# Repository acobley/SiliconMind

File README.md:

View this project on [CADLAB.io](https://cadlab.io/node/794). 

# SiliconMind
PCB3 is a test release.  
**Do not use** . Unwired airwire on PCB.
Use the hardware files

Pure Keys aec-pcb3.sch
Pure Keys aec-pcb3.brd

PCB2 is a working release.  Use the hardware files

Pure Keys aec-pcb2.sch
Pure Keys aec-pcb2.brd

**make sure that the 20 way header(keyboard connector) is soldered on so the connector is on the otherside of the board to the components. **

**Button 1** controls the mode. Starts in Polyphonc mode.  
Press once (2 flashes) for split mode.  CV1/Trig1 is lower half of keyboard. CV2/Trig2 is upper
Press again (3 flashes for mono mode.  CV1/Trig 1 only
Press again (1 flash) to return to poly mode.

**Button 2* is record/play mode
Press and hold (button flashes when ready) to enter record mode.  The note on each trig in will be recorded (up to 64), the note length is **not** recorded.  When finished press once to exit record mode.   Press once (quickly) to enter play mode.

For step type recording use a manual trigger press.

**Note** Will only record the bottom note, best used in Mono mode for recording.   In playback mode will output on CV1/Trig1 and other notes are shifted up one.  In Split mode upper half of keyboard is available.

**Glide** 
Controls the Portamento rate.  Works in Mono/Poly mode.  In Split mode only upper half of keyboard is glided.

-------------------------------------------------------------------

This is a project to create a voltage control keyboard for Eurorack Synths.  The aim is to create a fourvoice polyphtonic keyboard, with no MIDI at all.

The hardware is based around the ATMEGA.

See alos Changelog.txt in Hardware

Software 

SiliconMind.ion is latest for aec-pcb2 First PCB hardware

                  Work in progress, in test !

Hardware Designs:

Pure Keys aec Original Design

Pure Keys aec-pcb1 First PCB  do not use

      	       Needs pull down resistors on	MK lines
                   5V Ref needs	 replacing with 3v version
                   Switch needs	 pull up, not down.
Pure Keys aec-pcb2. 

                   Changes in pcb1 are rolled into this
                   Pure Keys aec-pcb2 In Progress

Pure Keys aec-pcb3-inProgress (obsolete)

	Next design in progress
	     	    Changes from pcb2 are rolled into this 
		    
Pure Keys aec-pcb3-smd-inProgress 

	SMD version.   Next design in progress
	     	    Changes from pcb2 are rolled into this 
Pure Keys aec-pcb3 

	SMD version.   **Do not use** Unwired airwire on PCB.
	
	     	    Changes from pcb2 are rolled into this

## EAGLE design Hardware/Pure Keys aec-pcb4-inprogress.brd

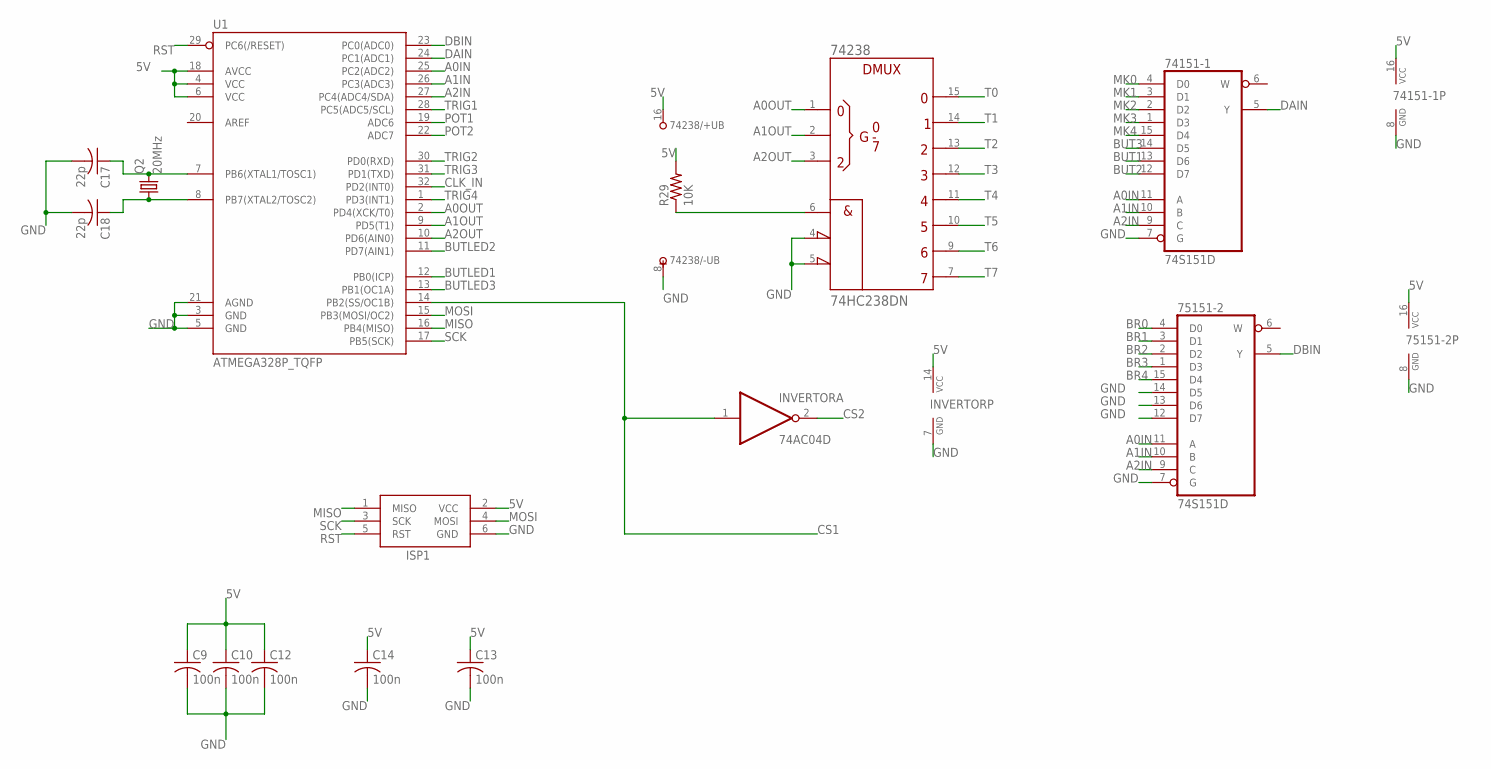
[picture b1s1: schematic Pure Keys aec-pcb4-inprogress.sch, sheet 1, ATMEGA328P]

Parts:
74151-1, 75151-2: 74S151D; SO16
74238: 74HC238DN; SO16
C9, C10, C12, C13, C14: 100n; C0805K
C17, C18: 22p; C0805K
INVERTOR: 74AC04D; SO14
ISP1: AVRISP-6; AVRISP
Q2: 20MHz; HC49UP
R29: 10K; R0805
U1: ATMEGA328P_TQFP; TQFP32-08

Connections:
5V: 74151-1.16 (VCC), 74238.16 (+UB), 75151-2.16 (VCC), C9.1, C10.1, C12.1, C13.1, C14.1, INVERTOR.14 (VCC), ISP1.2 (VCC), R29.2, U1.4 (VCC), U1.6 (VCC), U1.18 (AVCC); also elsewhere on the board
A0IN: 74151-1.11 (A), 75151-2.11 (A), U1.25 (PC2(ADC2))
A0OUT: 74238.1 (A), U1.2 (PD4(XCK/T0))
A1IN: 74151-1.10 (B), 75151-2.10 (B), U1.26 (PC3(ADC3))
A1OUT: 74238.2 (B), U1.9 (PD5(T1))
A2IN: 74151-1.9 (C), 75151-2.9 (C), U1.27 (PC4(ADC4/SDA))
A2OUT: 74238.3 (C), U1.10 (PD6(AIN0))
BR0: 75151-2.4 (D0); also elsewhere on the board
BR1: 75151-2.3 (D1); also elsewhere on the board
BR2: 75151-2.2 (D2); also elsewhere on the board
BR3: 75151-2.1 (D3); also elsewhere on the board
BR4: 75151-2.15 (D4); also elsewhere on the board
BUT1: 74151-1.13 (D6); also elsewhere on the board
BUT2: 74151-1.12 (D7); also elsewhere on the board
BUT3: 74151-1.14 (D5); also elsewhere on the board
BUTLED1: U1.12 (PB0(ICP)); also elsewhere on the board
BUTLED2: U1.11 (PD7(AIN1)); also elsewhere on the board
BUTLED3: U1.13 (PB1(OC1A)); also elsewhere on the board
CLK_IN: U1.32 (PD2(INT0)); also elsewhere on the board
CS1: INVERTOR.1 (I), U1.14 (PB2(SS/OC1B)); also elsewhere on the board
CS2: INVERTOR.2 (O); also elsewhere on the board
DAIN: 74151-1.5 (Y), U1.24 (PC1(ADC1))
DBIN: 75151-2.5 (Y), U1.23 (PC0(ADC0))
ENOUT1: 74238.6 (G1), R29.1
GND: 74151-1.7 (G), 74151-1.8 (GND), 74238.4 (!G2A), 74238.5 (!G2B), 74238.8 (-UB), 75151-2.7 (G), 75151-2.8 (GND), 75151-2.12 (D7), 75151-2.13 (D6), 75151-2.14 (D5), C9.2, C10.2, C12.2, C13.2, C14.2, C17.2, C18.2, INVERTOR.7 (GND), ISP1.6 (GND), U1.3 (GND), U1.5 (GND), U1.21 (AGND); also elsewhere on the board
MISO: ISP1.1 (MISO), U1.16 (PB4(MISO))
MK0: 74151-1.4 (D0); also elsewhere on the board
MK1: 74151-1.3 (D1); also elsewhere on the board
MK2: 74151-1.2 (D2); also elsewhere on the board
MK3: 74151-1.1 (D3); also elsewhere on the board
MK4: 74151-1.15 (D4); also elsewhere on the board
MOSI: ISP1.4 (MOSI), U1.15 (PB3(MOSI/OC2)); also elsewhere on the board
unnamed: C17.1, Q2.2, U1.7 (PB6(XTAL1/TOSC1))
unnamed: C18.1, Q2.1, U1.8 (PB7(XTAL2/TOSC2))
POT1: U1.19 (ADC6); also elsewhere on the board
POT2: U1.22 (ADC7); also elsewhere on the board
RST: ISP1.5 (RST), U1.29 (PC6(/RESET))
SCK: ISP1.3 (SCK), U1.17 (PB5(SCK)); also elsewhere on the board
T0: 74238.15 (Y0); also elsewhere on the board
T1: 74238.14 (Y1); also elsewhere on the board
T2: 74238.13 (Y2); also elsewhere on the board
T3: 74238.12 (Y3); also elsewhere on the board
T4: 74238.11 (Y4); also elsewhere on the board
T5: 74238.10 (Y5); also elsewhere on the board
T6: 74238.9 (Y6); also elsewhere on the board
T7: 74238.7 (Y7); also elsewhere on the board
TRIG1: U1.28 (PC5(ADC5/SCL)); also elsewhere on the board
TRIG2: U1.30 (PD0(RXD)); also elsewhere on the board
TRIG3: U1.31 (PD1(TXD)); also elsewhere on the board
TRIG4: U1.1 (PD3(INT1)); also elsewhere on the board

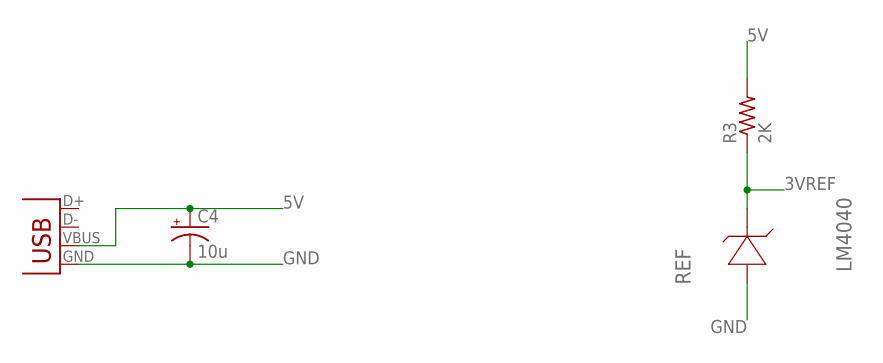
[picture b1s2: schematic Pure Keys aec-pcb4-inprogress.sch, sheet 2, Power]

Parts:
C4: 10u; 153CLV-0505
JP2: USB-B; USB-B-PTH
R3: 2K; R0805
REF: LM4040; SOT95P237X112-3N; MPN LM4040A30IDBZT

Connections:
3VREF: R3.1, REF.1 (CATHODE); also elsewhere on the board
5V: C4.+, JP2.VBUS, R3.2; also elsewhere on the board
GND: C4.-, JP2.GND, REF.2 (ANODE); also elsewhere on the board

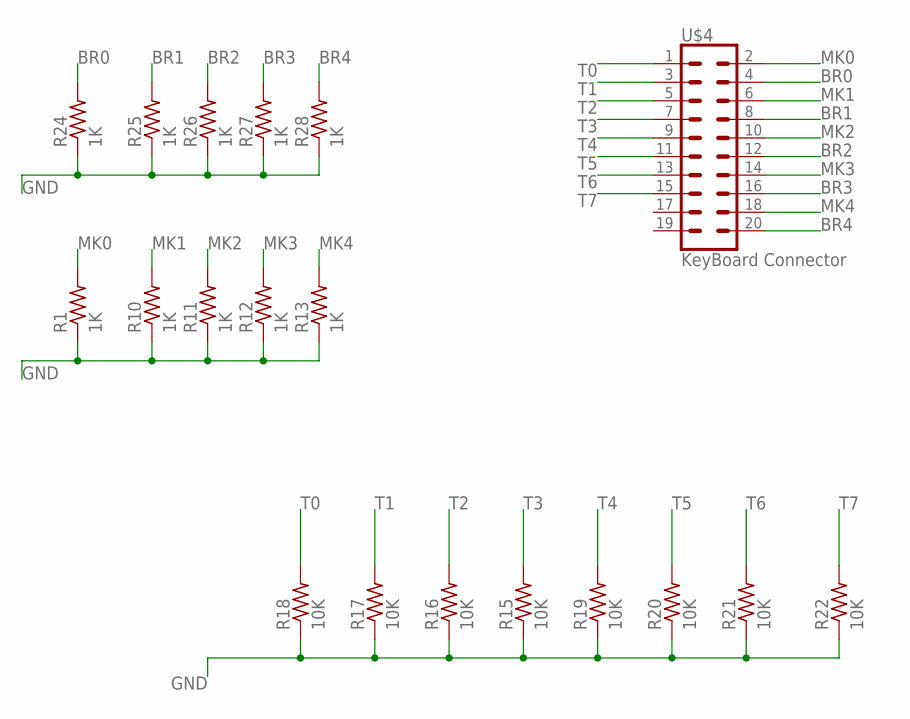
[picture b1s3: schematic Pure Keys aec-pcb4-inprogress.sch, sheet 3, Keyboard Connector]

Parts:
R1, R10, R11, R12, R13, R24, R25, R26, R27, R28: 1K; R0805
R15, R16, R17, R18, R19, R20, R21, R22: 10K; R0805
U$4: KeyBoard Connector; 2X10

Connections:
BR0: R24.2, U$4.4; also elsewhere on the board
BR1: R25.2, U$4.8; also elsewhere on the board
BR2: R26.2, U$4.12; also elsewhere on the board
BR3: R27.2, U$4.16; also elsewhere on the board
BR4: R28.2, U$4.20; also elsewhere on the board
GND: R1.1, R10.1, R11.1, R12.1, R13.1, R15.1, R16.1, R17.1, R18.1, R19.1, R20.1, R21.1, R22.1, R24.1, R25.1, R26.1, R27.1, R28.1; also elsewhere on the board
MK0: R1.2, U$4.2; also elsewhere on the board
MK1: R10.2, U$4.6; also elsewhere on the board
MK2: R11.2, U$4.10; also elsewhere on the board
MK3: R12.2, U$4.14; also elsewhere on the board
MK4: R13.2, U$4.18; also elsewhere on the board
T0: R18.2, U$4.1; also elsewhere on the board
T1: R17.2, U$4.3; also elsewhere on the board
T2: R16.2, U$4.5; also elsewhere on the board
T3: R15.2, U$4.7; also elsewhere on the board
T4: R19.2, U$4.9; also elsewhere on the board
T5: R20.2, U$4.11; also elsewhere on the board
T6: R21.2, U$4.13; also elsewhere on the board
T7: R22.2, U$4.15; also elsewhere on the board

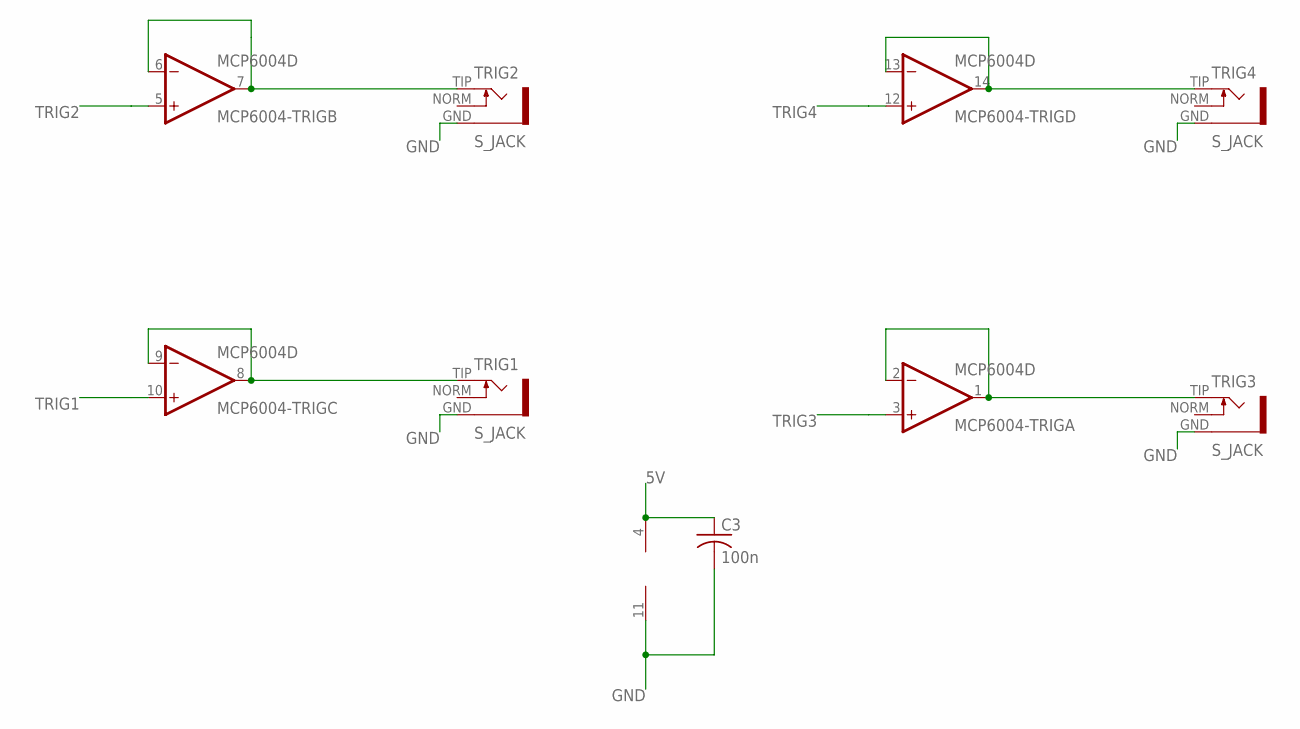
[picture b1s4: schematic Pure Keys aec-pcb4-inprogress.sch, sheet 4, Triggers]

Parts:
C3: 100n; C0805K
MCP6004-TRIG: MCP6004D; SO14
TRIG1, TRIG2, TRIG3, TRIG4: S_JACK

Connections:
5V: C3.1, MCP6004-TRIG.4 (V+); also elsewhere on the board
GND: C3.2, MCP6004-TRIG.11 (V-), TRIG1.GND, TRIG2.GND, TRIG3.GND, TRIG4.GND; also elsewhere on the board
unnamed: MCP6004-TRIG.6 (-IN), MCP6004-TRIG.7 (OUT), TRIG2.TIP
unnamed: MCP6004-TRIG.8 (OUT), MCP6004-TRIG.9 (-IN), TRIG1.TIP
unnamed: MCP6004-TRIG.13 (-IN), MCP6004-TRIG.14 (OUT), TRIG4.TIP
unnamed: MCP6004-TRIG.1 (OUT), MCP6004-TRIG.2 (-IN), TRIG3.TIP
TRIG1: MCP6004-TRIG.10 (+IN); also elsewhere on the board
TRIG2: MCP6004-TRIG.5 (+IN); also elsewhere on the board
TRIG3: MCP6004-TRIG.3 (+IN); also elsewhere on the board
TRIG4: MCP6004-TRIG.12 (+IN); also elsewhere on the board

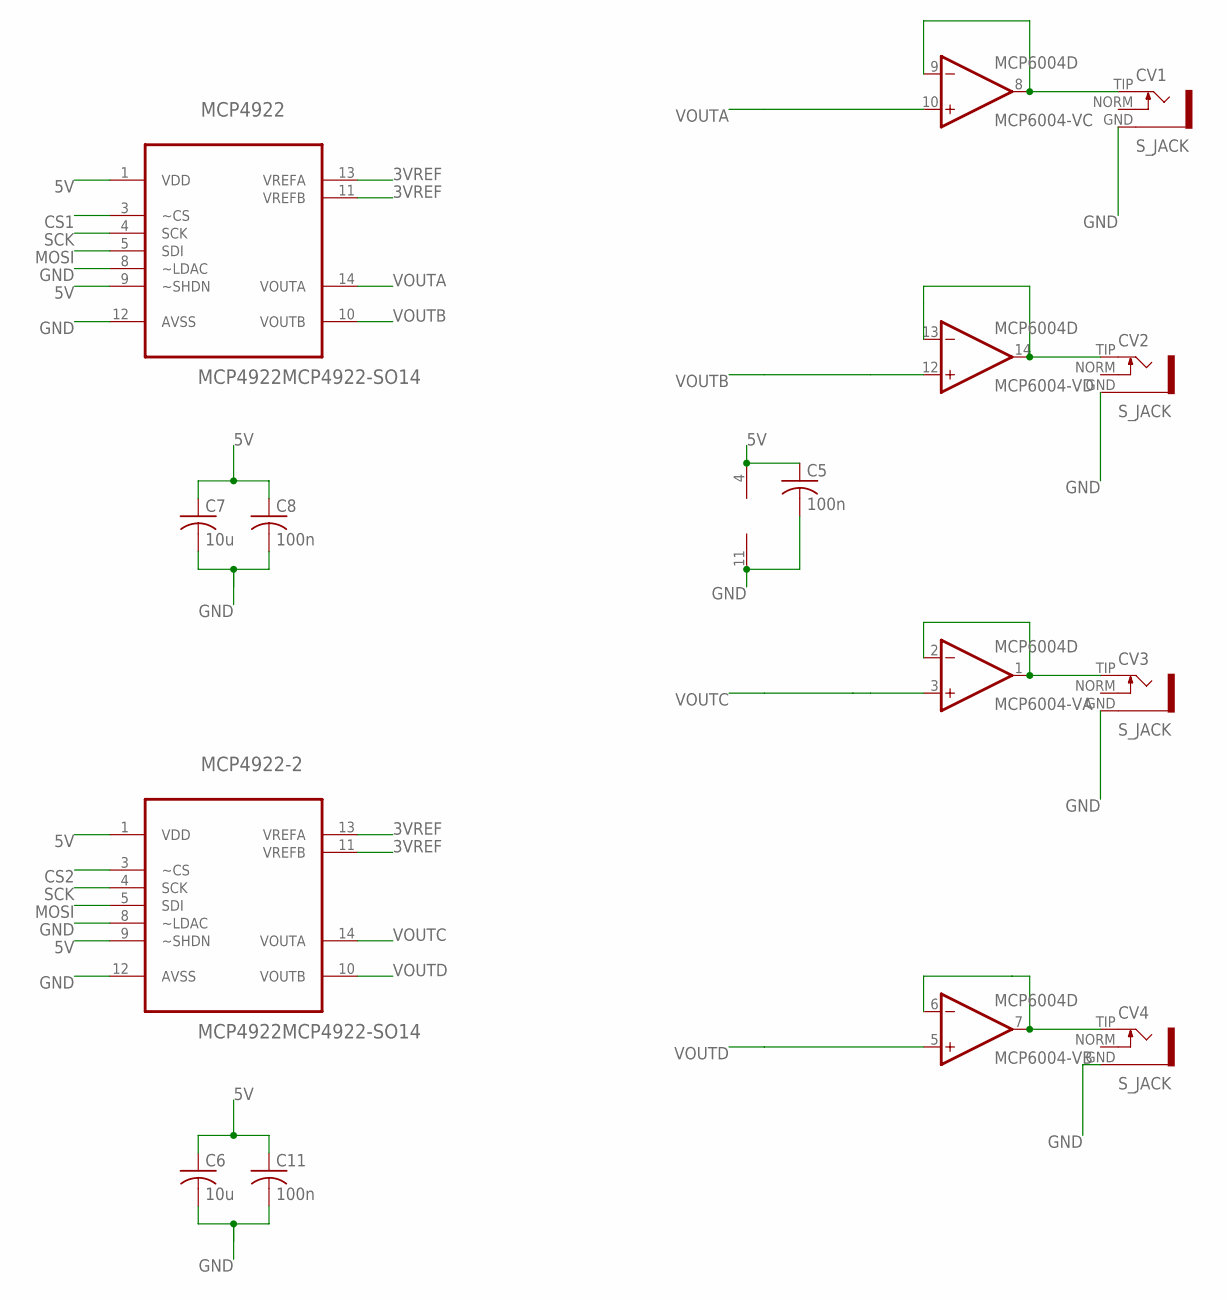
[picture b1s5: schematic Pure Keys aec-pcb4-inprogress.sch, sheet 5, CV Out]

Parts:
C5, C8, C11: 100n; C0805K
C6, C7: 10u; C0805K
CV1, CV2, CV3, CV4: S_JACK
MCP4922, MCP4922-2: MCP4922MCP4922-SO14; SO14
MCP6004-V: MCP6004D; SO14

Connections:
3VREF: MCP4922.11 (VREFB), MCP4922.13 (VREFA), MCP4922-2.11 (VREFB), MCP4922-2.13 (VREFA); also elsewhere on the board
5V: C5.1, C6.1, C7.1, C8.1, C11.1, MCP4922.1 (VDD), MCP4922.9 (~SHDN), MCP4922-2.1 (VDD), MCP4922-2.9 (~SHDN), MCP6004-V.4 (V+); also elsewhere on the board
CS1: MCP4922.3 (~CS); also elsewhere on the board
CS2: MCP4922-2.3 (~CS); also elsewhere on the board
GND: C5.2, C6.2, C7.2, C8.2, C11.2, CV1.GND, CV2.GND, CV3.GND, CV4.GND, MCP4922.8 (~LDAC), MCP4922.12 (AVSS), MCP4922-2.8 (~LDAC), MCP4922-2.12 (AVSS), MCP6004-V.11 (V-); also elsewhere on the board
MOSI: MCP4922.5 (SDI), MCP4922-2.5 (SDI); also elsewhere on the board
unnamed: CV1.TIP, MCP6004-V.8 (OUT), MCP6004-V.9 (-IN)
unnamed: CV4.TIP, MCP6004-V.6 (-IN), MCP6004-V.7 (OUT)
unnamed: CV3.TIP, MCP6004-V.1 (OUT), MCP6004-V.2 (-IN)
unnamed: CV2.TIP, MCP6004-V.13 (-IN), MCP6004-V.14 (OUT)
SCK: MCP4922.4 (SCK), MCP4922-2.4 (SCK); also elsewhere on the board
VOUTA: MCP4922.14 (VOUTA), MCP6004-V.10 (+IN)
VOUTB: MCP4922.10 (VOUTB), MCP6004-V.12 (+IN)
VOUTC: MCP4922-2.14 (VOUTA), MCP6004-V.3 (+IN)
VOUTD: MCP4922-2.10 (VOUTB), MCP6004-V.5 (+IN)

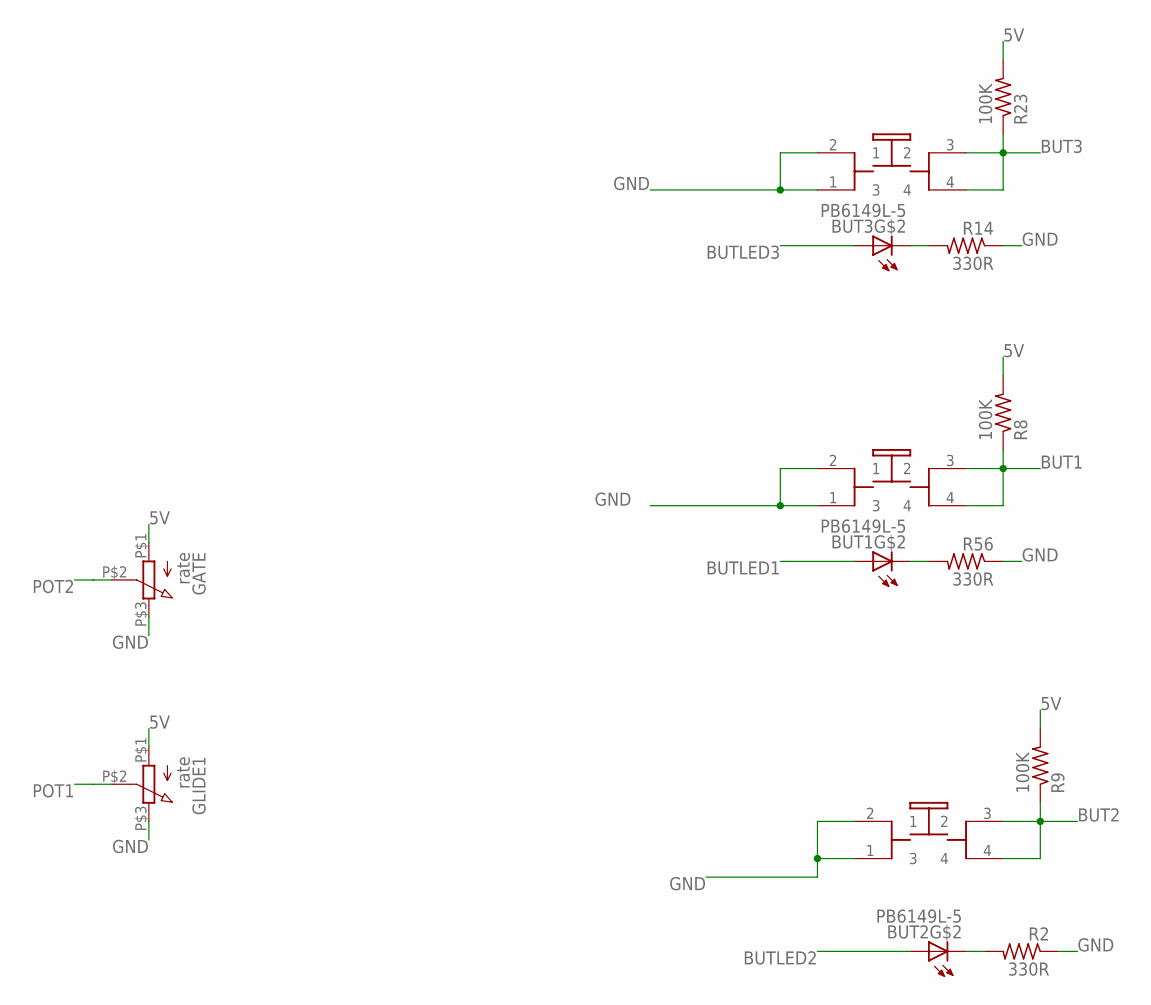
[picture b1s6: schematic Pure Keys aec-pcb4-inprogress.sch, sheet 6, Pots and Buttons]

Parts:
BUT1, BUT2, BUT3: PB6149L-5; PB6149L
GATE: rate; POT
GLIDE1: rate; POT
R2, R14, R56: 330R; R0805
R8, R9, R23: 100K; R0805

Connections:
5V: GATE.P$1 (1), GLIDE1.P$1 (1), R8.2, R9.2, R23.2; also elsewhere on the board
BUT1: BUT1.3 (2), BUT1.4, R8.1; also elsewhere on the board
BUT2: BUT2.3 (2), BUT2.4, R9.1; also elsewhere on the board
BUT3: BUT3.3 (2), BUT3.4, R23.1; also elsewhere on the board
BUTLED1: BUT1.A; also elsewhere on the board
BUTLED2: BUT2.A; also elsewhere on the board
BUTLED3: BUT3.A; also elsewhere on the board
GND: BUT1.1 (3), BUT1.2 (1), BUT2.1 (3), BUT2.2 (1), BUT3.1 (3), BUT3.2 (1), GATE.P$3 (3), GLIDE1.P$3 (3), R2.1, R14.1, R56.1; also elsewhere on the board
unnamed: BUT3.K (C), R14.2
unnamed: BUT2.K (C), R2.2
unnamed: BUT1.K (C), R56.2
POT1: GLIDE1.P$2 (2); also elsewhere on the board
POT2: GATE.P$2 (2); also elsewhere on the board

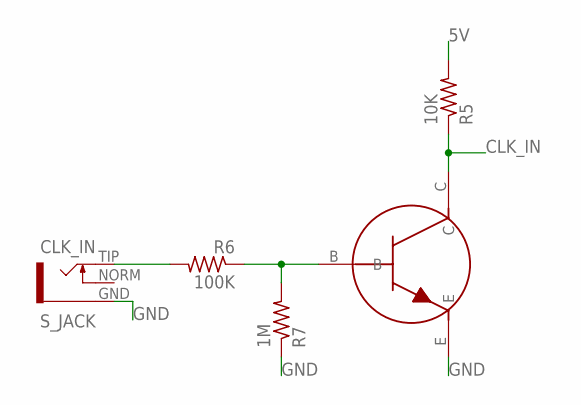
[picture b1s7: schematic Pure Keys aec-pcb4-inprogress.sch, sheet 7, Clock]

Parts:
CLK_IN: S_JACK
CLOCK: 2N3904; TRANSISTOR_SINGLE_N-TYPE
R5: 10K; R0805
R6: 100K; R0805
R7: 1M; R0805

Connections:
5V: R5.2; also elsewhere on the board
CLK_IN: CLOCK.C, R5.1; also elsewhere on the board
GND: CLK_IN.GND, CLOCK.E, R7.1; also elsewhere on the board
unnamed: CLOCK.B, R6.1, R7.2
unnamed: CLK_IN.TIP, R6.2

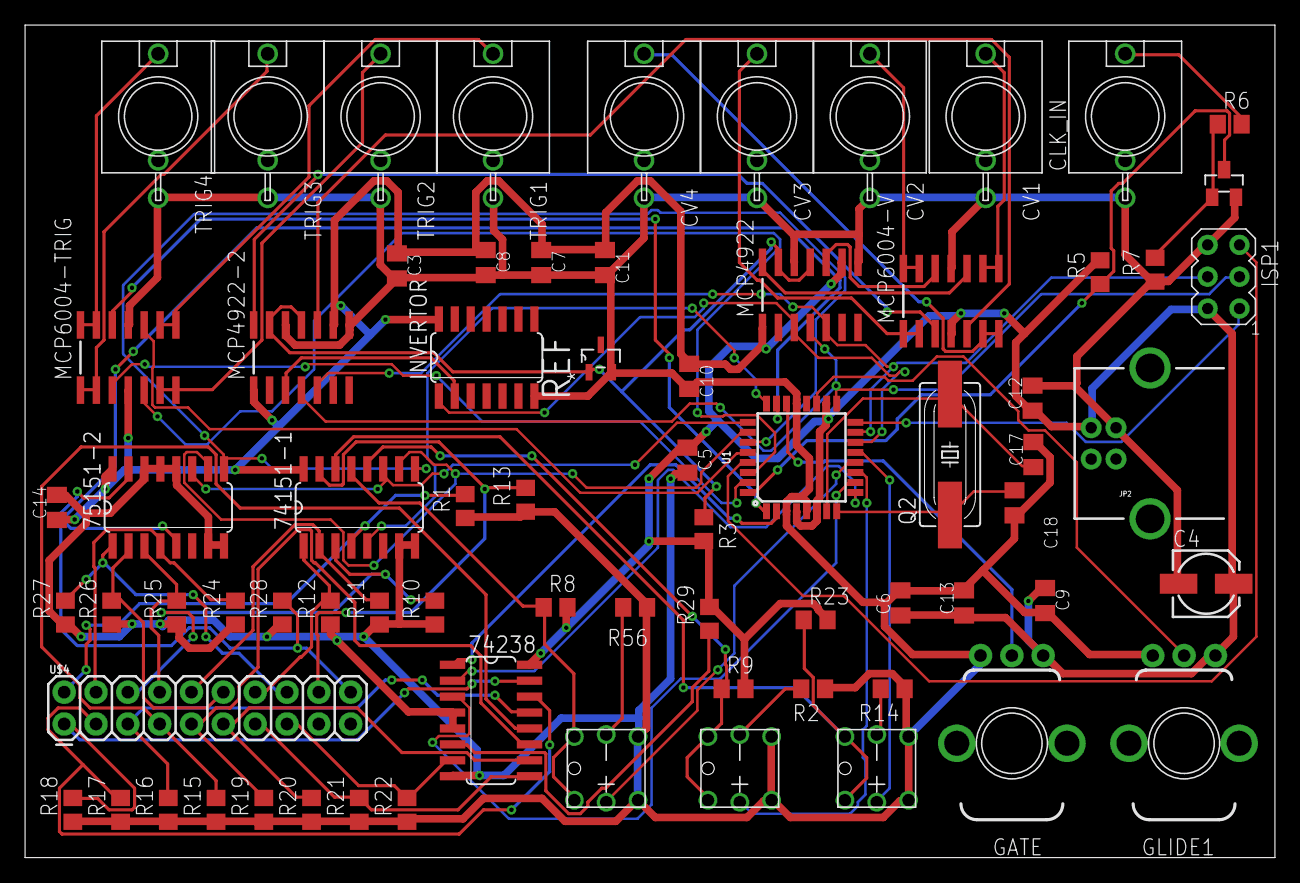
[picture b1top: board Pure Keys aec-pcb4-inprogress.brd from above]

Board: 2 copper layers, 99.7 x 66.4 mm, 72 parts (0 on the bottom side), 68 nets.

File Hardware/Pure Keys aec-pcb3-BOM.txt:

"Part";"Value";"Device";"Package";"Description";"MF";"MPN";"OC_FARNELL";"OC_NEWARK";"PACKAGE";"PROD_ID";"RC-PART";"RS-PART";"SUPPLIER";"VALUE";
"74151-1";"74S151D";"74S151D";"SO16";"Data SELECTOR/MULTIPLEXER";"";"";"";"";"";"";"";"436-7436";"";"";
"74238";"74HC238DN";"74HC238DN";"SO16";"1 of 8 noninverting DECODER/DEMULTIPLEXER";"";"";"";"";"";"";"";"483-6487 (10off)";"";"";
"75151-2";"74S151D";"74S151D";"SO16";"Data SELECTOR/MULTIPLEXER";"";"";"";"";"";"";"";"436-7436";"";"";
"BUT1";"PB6149L-5";"PB6149L-5";"PB6149L";"";"";"";"";"";"";"";"";"";"";"";
"BUT2";"PB6149L-5";"PB6149L-5";"PB6149L";"";"";"";"";"";"";"";"";"";"";"";
"BUT3";"PB6149L-5";"PB6149L-5";"PB6149L";"";"";"";"";"";"";"";"";"";"";"";
"C3";"100n";"C-USC0805K";"C0805K";"CAPACITOR, American symbol";"";"";"";"";"";"";"";"";"";"";
"C4";"10u";"CPOL-US153CLV-0505";"153CLV-0505";"POLARIZED CAPACITOR, American symbol";"";"";"";"";"";"";"";"";"";"";
"C5";"100n";"C-USC0805K";"C0805K";"CAPACITOR, American symbol";"";"";"";"";"";"";"";"";"";"";
"C6";"10u";"C-USC0805K";"C0805K";"CAPACITOR, American symbol";"";"";"";"";"";"";"";"";"";"";
"C7";"10u";"C-USC0805K";"C0805K";"CAPACITOR, American symbol";"";"";"";"";"";"";"";"";"";"";
"C8";"100n";"C-USC0805K";"C0805K";"CAPACITOR, American symbol";"";"";"";"";"";"";"";"";"";"";
"C9";"100n";"C-USC0805K";"C0805K";"CAPACITOR, American symbol";"";"";"";"";"";"";"";"";"";"";
"C10";"100n";"C-USC0805K";"C0805K";"CAPACITOR, American symbol";"";"";"";"";"";"";"";"";"";"";
"C11";"100n";"C-USC0805K";"C0805K";"CAPACITOR, American symbol";"";"";"";"";"";"";"";"";"";"";
"C12";"100n";"C-USC0805K";"C0805K";"CAPACITOR, American symbol";"";"";"";"";"";"";"";"";"";"";
"C13";"100n";"C-USC0805K";"C0805K";"CAPACITOR, American symbol";"";"";"";"";"";"";"";"";"";"";
"C14";"100n";"C-USC0805K";"C0805K";"CAPACITOR, American symbol";"";"";"";"";"";"";"";"";"";"";
"C17";"22p";"C-USC0805K";"C0805K";"CAPACITOR, American symbol";"";"";"";"";"";"";"";"";"";"";
"C18";"22p";"C-USC0805K";"C0805K";"CAPACITOR, American symbol";"";"";"";"";"";"";"";"";"";"";
"CLK_IN";"S_JACK";"S_JACK";"S_JACK";"";"";"";"";"";"";"";"";"";"";"";
"CLOCK";"2N3904";"TRANSISTOR_MMBT3904";"TRANSISTOR_SINGLE_N-TYPE";"";"";"";"";"";"";"";"";"725-8616 ";"";"";
"CV1";"S_JACK";"S_JACK";"S_JACK";"";"";"";"";"";"";"";"";"";"";"";
"CV2";"S_JACK";"S_JACK";"S_JACK";"";"";"";"";"";"";"";"";"";"";"";
"CV3";"S_JACK";"S_JACK";"S_JACK";"";"";"";"";"";"";"";"";"";"";"";
"CV4";"S_JACK";"S_JACK";"S_JACK";"";"";"";"";"";"";"";"";"";"";"";
"GATE";"rate";"9MMPOT";"POT";"";"";"";"";"";"";"";"";"";"";"";
"GLIDE1";"rate";"9MMPOT";"POT";"";"";"";"";"";"";"";"";"";"";"";
"INVERTOR";"74AC04D";"74AC04D";"SO14";"Hex INVERTER";"";"";"";"";"";"";"171-3461 (50 off)";"";"";"";
"ISP1";"AVRISP-6";"AVRISP-6";"AVRISP";"AVR ISP HEADER";"";"";"";"";"";"";"";"";"";"";
"JP2";"USB-B";"USBPTH";"USB-B-PTH";"USB Connectors";"";"";"";"";"";"CONN-08278";"";"";"";"USB-B";
"MCP4922";"MCP4922MCP4922-SO14";"MCP4922MCP4922-SO14";"SO14";"";"";"";"";"";"";"";"";"402-910 ";"";"";
"MCP4922-2";"MCP4922MCP4922-SO14";"MCP4922MCP4922-SO14";"SO14";"";"";"";"";"";"";"";"";"";"";"";
"MCP6004-TRIG";"MCP6004D";"MCP6004D";"SO14";"OP AMP";"";"";"";"";"";"";"";"628-3481 (10)";"";"";
"MCP6004-V";"MCP6004D";"MCP6004D";"SO14";"OP AMP";"";"";"";"";"";"";"";"628-3481 (10)";"";"";
"Q2";"20MHz";"CRYSTALHC49UP";"HC49UP";"CRYSTAL";"";"";"unknown";"unknown";"";"";"";"";"";"";
"R1";"1K";"R-US_R0805";"R0805";"RESISTOR, American symbol";"";"";"";"";"";"";"";"223-0427";"";"";
"R2";"330R";"R-US_R0805";"R0805";"RESISTOR, American symbol";"";"";"";"";"";"";"";"";"";"";
"R3";"2K";"R-US_R0805";"R0805";"RESISTOR, American symbol";"";"";"";"";"";"";"";"";"";"";
"R5";"10K";"R-US_R0805";"R0805";"RESISTOR, American symbol";"";"";"";"";"";"";"";"";"";"";
"R6";"100K";"R-US_R0805";"R0805";"RESISTOR, American symbol";"";"";"";"";"";"";"";"";"";"";
"R7";"1M";"R-US_R0805";"R0805";"RESISTOR, American symbol";"";"";"";"";"";"";"";"";"";"";
"R8";"100K";"R-US_R0805";"R0805";"RESISTOR, American symbol";"";"";"";"";"";"";"";"";"";"";
"R9";"100K";"R-US_R0805";"R0805";"RESISTOR, American symbol";"";"";"";"";"";"";"";"";"";"";
"R10";"1K";"R-US_R0805";"R0805";"RESISTOR, American symbol";"";"";"";"";"";"";"";"223-0427";"";"";
"R11";"1K";"R-US_R0805";"R0805";"RESISTOR, American symbol";"";"";"";"";"";"";"";"223-0427";"";"";
"R12";"1K";"R-US_R0805";"R0805";"RESISTOR, American symbol";"";"";"";"";"";"";"";"223-0427";"";"";
"R13";"1K";"R-US_R0805";"R0805";"RESISTOR, American symbol";"";"";"";"";"";"";"";"223-0427";"";"";
"R14";"330R";"R-US_R0805";"R0805";"RESISTOR, American symbol";"";"";"";"";"";"";"";"";"";"";
"R15";"10K";"R-US_R0805";"R0805";"RESISTOR, American symbol";"";"";"";"";"";"";"";"";"";"";
"R16";"10K";"R-US_R0805";"R0805";"RESISTOR, American symbol";"";"";"";"";"";"";"";"";"";"";
"R17";"10K";"R-US_R0805";"R0805";"RESISTOR, American symbol";"";"";"";"";"";"";"";"";"";"";
"R18";"10K";"R-US_R0805";"R0805";"RESISTOR, American symbol";"";"";"";"";"";"";"";"";"";"";
"R19";"10K";"R-US_R0805";"R0805";"RESISTOR, American symbol";"";"";"";"";"";"";"";"";"";"";
"R20";"10K";"R-US_R0805";"R0805";"RESISTOR, American symbol";"";"";"";"";"";"";"";"";"";"";
"R21";"10K";"R-US_R0805";"R0805";"RESISTOR, American symbol";"";"";"";"";"";"";"";"";"";"";
"R22";"10K";"R-US_R0805";"R0805";"RESISTOR, American symbol";"";"";"";"";"";"";"";"";"";"";
"R23";"100K";"R-US_R0805";"R0805";"RESISTOR, American symbol";"";"";"";"";"";"";"";"";"";"";
"R24";"1K";"R-US_R0805";"R0805";"RESISTOR, American symbol";"";"";"";"";"";"";"";"223-0427";"";"";
"R25";"1K";"R-US_R0805";"R0805";"RESISTOR, American symbol";"";"";"";"";"";"";"";"223-0427";"";"";
"R26";"1K";"R-US_R0805";"R0805";"RESISTOR, American symbol";"";"";"";"";"";"";"";"223-0427";"";"";
"R27";"1K";"R-US_R0805";"R0805";"RESISTOR, American symbol";"";"";"";"";"";"";"";"223-0427";"";"";
"R28";"1K";"R-US_R0805";"R0805";"RESISTOR, American symbol";"";"";"";"";"";"";"";"223-0427";"";"";
"R29";"10K";"R-US_R0805";"R0805";"RESISTOR, American symbol";"";"";"";"";"";"";"";"";"";"";
"R56";"330R";"R-US_R0805";"R0805";"RESISTOR, American symbol";"";"";"";"";"";"";"";"";"";"";
"REF";"LM4040";"LM4040A30IDBZT";"SOT95P237X112-3N";"PRECISION MICROPOWER SHUNT VOLTAGE REFERENCE";"";"LM4040A30IDBZT";"1755108";"58K5870";"3-SOT-23";"";"";"809-6343";"TEXAS INSTRUMENTS";"";
"TRIG1";"S_JACK";"S_JACK";"S_JACK";"";"";"";"";"";"";"";"";"";"";"";
"TRIG2";"S_JACK";"S_JACK";"S_JACK";"";"";"";"";"";"";"";"";"";"";"";
"TRIG3";"S_JACK";"S_JACK";"S_JACK";"";"";"";"";"";"";"";"";"";"";"";
"TRIG4";"S_JACK";"S_JACK";"S_JACK";"";"";"";"";"";"";"";"";"";"";"";
"U$4";"KeyBoard Connector";"CONN_10X2";"2X10";"Multi connection point. Often used as Generic Header-pin footprint for 0.1 inch spaced/style header connections";"";"";"";"";"";"";"";"669-5364";"";"";
"U1";"ATMEGA328P_TQFP";"ATMEGA328P_TQFP";"TQFP32-08";"Popular 328P in QFP";"";"";"";"";"";"IC-09069";"";"131-0271";"";"ATMEGA328P_TQFP";

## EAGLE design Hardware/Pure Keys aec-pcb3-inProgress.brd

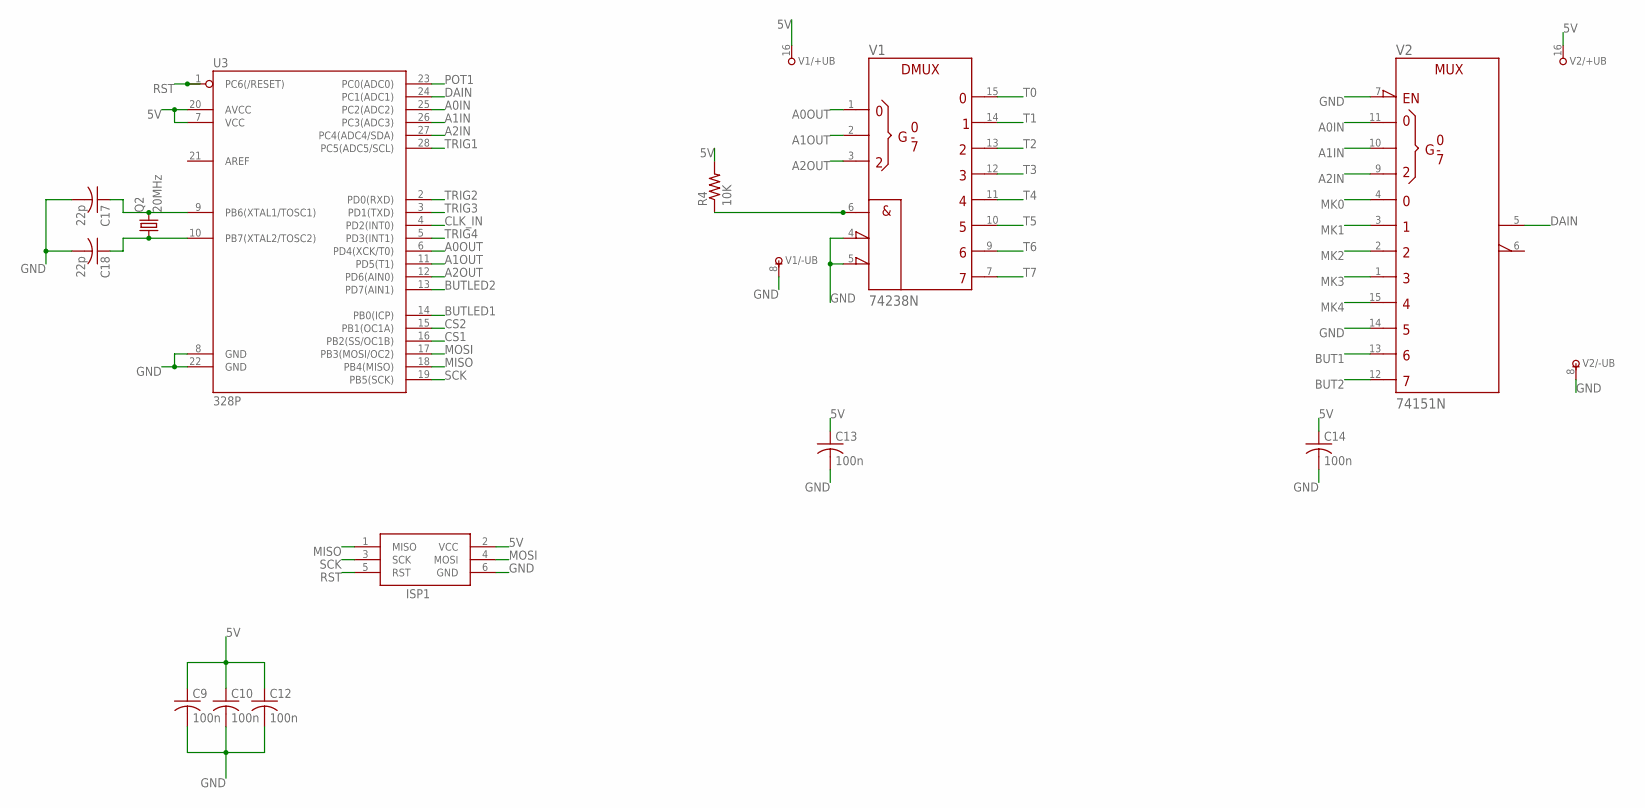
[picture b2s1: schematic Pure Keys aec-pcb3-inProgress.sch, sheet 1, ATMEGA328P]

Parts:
C9, C10, C12, C13, C14: 100n; C0805K
C17, C18: 22p; C0805K
ISP1: AVRISP-6; AVRISP
Q2: 20MHz; HC49UP
R4: 10K; R0805
U3: 328P; DIP28
V1: 74238N; DIL16
V2: 74151N; DIL16

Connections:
5V: C9.1, C10.1, C12.1, C13.1, C14.1, ISP1.2 (VCC), R4.2, U3.7 (VCC), U3.20 (AVCC), V1.16 (+UB), V2.16 (+UB); also elsewhere on the board
A0IN: U3.25 (PC2(ADC2)), V2.11 (A)
A0OUT: U3.6 (PD4(XCK/T0)), V1.1 (A)
A1IN: U3.26 (PC3(ADC3)), V2.10 (B)
A1OUT: U3.11 (PD5(T1)), V1.2 (B)
A2IN: U3.27 (PC4(ADC4/SDA)), V2.9 (C)
A2OUT: U3.12 (PD6(AIN0)), V1.3 (C)
BUT1: V2.13 (D6); also elsewhere on the board
BUT2: V2.12 (D7); also elsewhere on the board
BUTLED1: U3.14 (PB0(ICP)); also elsewhere on the board
BUTLED2: U3.13 (PD7(AIN1)); also elsewhere on the board
CLK_IN: U3.4 (PD2(INT0)); also elsewhere on the board
CS1: U3.16 (PB2(SS/OC1B)); also elsewhere on the board
CS2: U3.15 (PB1(OC1A)); also elsewhere on the board
DAIN: U3.24 (PC1(ADC1)), V2.5 (Y)
ENOUT: R4.1, V1.6 (G1)
GND: C9.2, C10.2, C12.2, C13.2, C14.2, C17.2, C18.2, ISP1.6 (GND), U3.8 (GND), U3.22 (GND), V1.4 (!G2A), V1.5 (!G2B), V1.8 (-UB), V2.7 (!G), V2.8 (-UB), V2.14 (D5); also elsewhere on the board
MISO: ISP1.1 (MISO), U3.18 (PB4(MISO))
MK0: V2.4 (D0); also elsewhere on the board
MK1: V2.3 (D1); also elsewhere on the board
MK2: V2.2 (D2); also elsewhere on the board
MK3: V2.1 (D3); also elsewhere on the board
MK4: V2.15 (D4); also elsewhere on the board
MOSI: ISP1.4 (MOSI), U3.17 (PB3(MOSI/OC2)); also elsewhere on the board
unnamed: C17.1, Q2.2, U3.9 (PB6(XTAL1/TOSC1))
unnamed: C18.1, Q2.1, U3.10 (PB7(XTAL2/TOSC2))
POT1: U3.23 (PC0(ADC0)); also elsewhere on the board
RST: ISP1.5 (RST), U3.1 (PC6(/RESET))
SCK: ISP1.3 (SCK), U3.19 (PB5(SCK)); also elsewhere on the board
T0: V1.15 (Y0); also elsewhere on the board
T1: V1.14 (Y1); also elsewhere on the board
T2: V1.13 (Y2); also elsewhere on the board
T3: V1.12 (Y3); also elsewhere on the board
T4: V1.11 (Y4); also elsewhere on the board
T5: V1.10 (Y5); also elsewhere on the board
T6: V1.9 (Y6); also elsewhere on the board
T7: V1.7 (Y7); also elsewhere on the board
TRIG1: U3.28 (PC5(ADC5/SCL)); also elsewhere on the board
TRIG2: U3.2 (PD0(RXD)); also elsewhere on the board
TRIG3: U3.3 (PD1(TXD)); also elsewhere on the board
TRIG4: U3.5 (PD3(INT1)); also elsewhere on the board

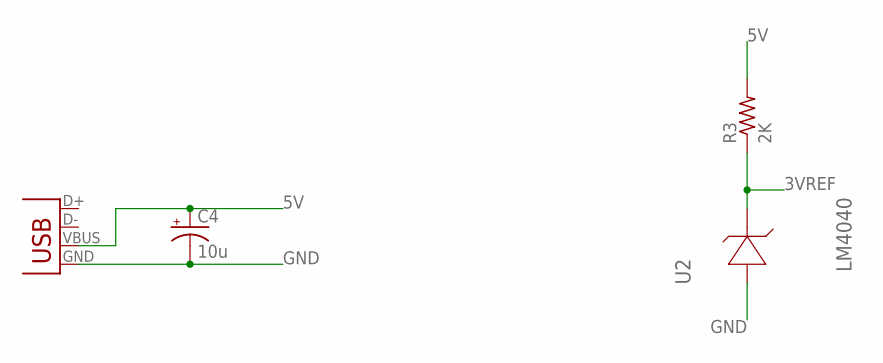
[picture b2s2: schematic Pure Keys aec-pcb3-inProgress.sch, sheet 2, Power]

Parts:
C4: 10u; 153CLV-0505
JP2: USB-B; USB-B-PTH
R3: 2K; R0805
U2: LM4040; SOT95P237X112-3N; MPN LM4040A30IDBZT

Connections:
3VREF: R3.1, U2.1 (CATHODE); also elsewhere on the board
5V: C4.+, JP2.VBUS, R3.2; also elsewhere on the board
GND: C4.-, JP2.GND, U2.2 (ANODE); also elsewhere on the board

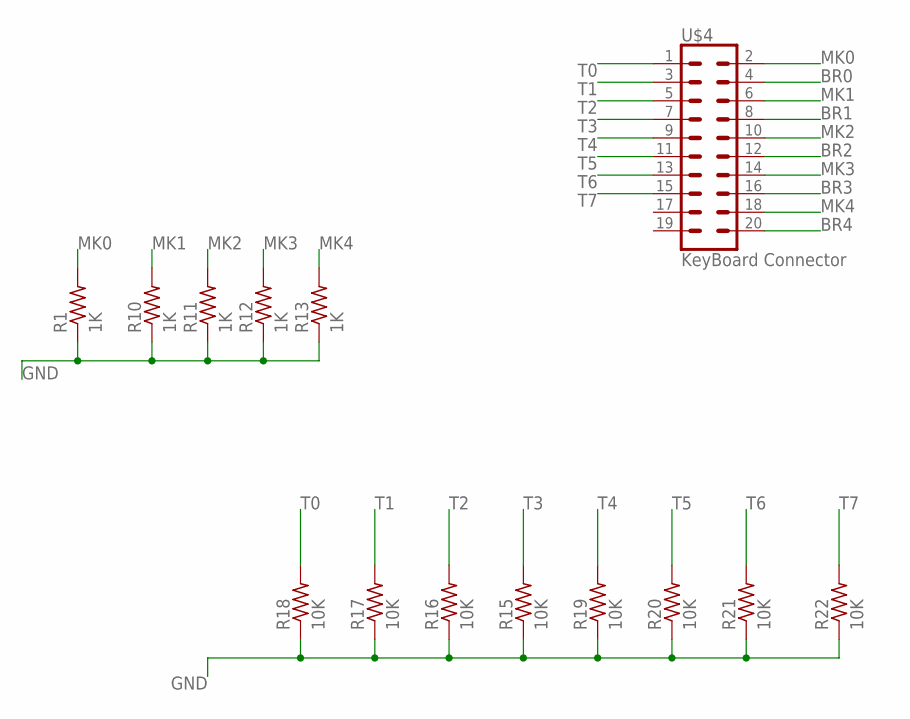
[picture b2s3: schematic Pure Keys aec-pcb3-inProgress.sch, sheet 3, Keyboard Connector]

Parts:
R1, R10, R11, R12, R13: 1K; R0805
R15, R16, R17, R18, R19, R20, R21, R22: 10K; R0805
U$4: KeyBoard Connector; 2X10

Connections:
BR0: U$4.4
BR1: U$4.8
BR2: U$4.12
BR3: U$4.16
BR4: U$4.20
GND: R1.1, R10.1, R11.1, R12.1, R13.1, R15.1, R16.1, R17.1, R18.1, R19.1, R20.1, R21.1, R22.1; also elsewhere on the board
MK0: R1.2, U$4.2; also elsewhere on the board
MK1: R10.2, U$4.6; also elsewhere on the board
MK2: R11.2, U$4.10; also elsewhere on the board
MK3: R12.2, U$4.14; also elsewhere on the board
MK4: R13.2, U$4.18; also elsewhere on the board
T0: R18.2, U$4.1; also elsewhere on the board
T1: R17.2, U$4.3; also elsewhere on the board
T2: R16.2, U$4.5; also elsewhere on the board
T3: R15.2, U$4.7; also elsewhere on the board
T4: R19.2, U$4.9; also elsewhere on the board
T5: R20.2, U$4.11; also elsewhere on the board
T6: R21.2, U$4.13; also elsewhere on the board
T7: R22.2, U$4.15; also elsewhere on the board

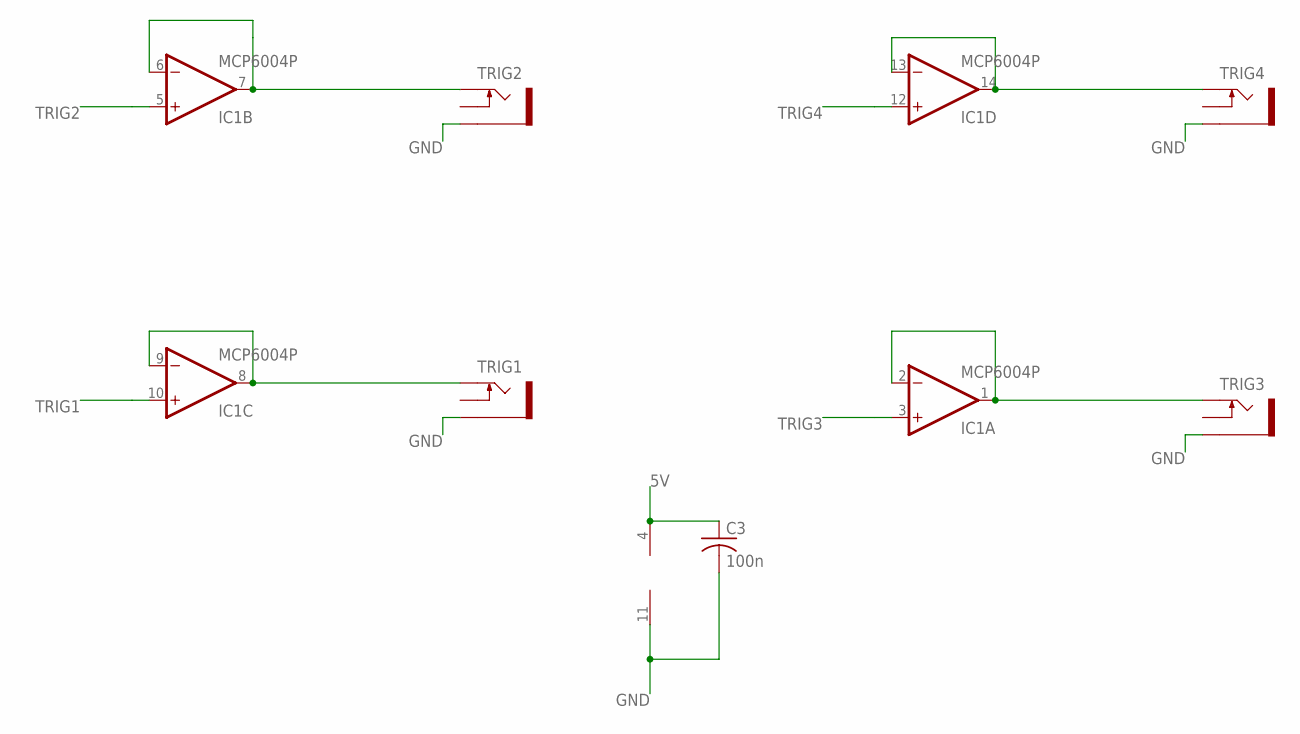
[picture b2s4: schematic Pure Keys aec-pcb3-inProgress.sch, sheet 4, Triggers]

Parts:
C3: 100n; C0805K
IC1: MCP6004P; DIL14
TRIG1, TRIG2, TRIG3, TRIG4: PJ302M

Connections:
5V: C3.1, IC1.4 (V+); also elsewhere on the board
GND: C3.2, IC1.11 (V-), TRIG1.GND (SLEEVE), TRIG2.GND (SLEEVE), TRIG3.GND (SLEEVE), TRIG4.GND (SLEEVE); also elsewhere on the board
unnamed: IC1.6 (-IN), IC1.7 (OUT), TRIG2.TIP
unnamed: IC1.8 (OUT), IC1.9 (-IN), TRIG1.TIP
unnamed: IC1.13 (-IN), IC1.14 (OUT), TRIG4.TIP
unnamed: IC1.1 (OUT), IC1.2 (-IN), TRIG3.TIP
TRIG1: IC1.10 (+IN); also elsewhere on the board
TRIG2: IC1.5 (+IN); also elsewhere on the board
TRIG3: IC1.3 (+IN); also elsewhere on the board
TRIG4: IC1.12 (+IN); also elsewhere on the board

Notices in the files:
parts and their libraries:
SparkFun-Connectors: Licensing: CC v3.0 Share-Alike You are welcome to use this library for commercial purposes.
SparkFun-IC-Microcontroller: Licensing: Creative Commons ShareAlike 4.0 International - https://creativecommons.org/licenses/by-sa/4.0
